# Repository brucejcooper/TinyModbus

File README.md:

# TinyModbus DALI Gateway

An ATtiny1604-based Modbus RTU to DALI gateway. It acts as a Modbus slave device and puts DALI frames on the wire on behalf of a master.

> ## The gateway is a stateless pipe
>
> **It caches nothing about the bus.** No arc levels, no status, no presence or
> dirty bitmaps, no group masks, no commissioning state, no scan cursors. The
> master submits opaque commands over a single function code; the gateway
> executes them in accept order and hands each result back exactly once, holding
> it until the master acks it. That is the whole contract.
>
> This is deliberate — "no cache of a cache": **the ballasts are the
> authority, the controller holds the one and only cache, the gateway holds
> none.** The consequences are worth stating plainly —
>
> - **A gateway reboot is consequence-free.** There is no state to lose, so the
>   class of bug where a rebooted gateway served zeroed registers and poisoned
>   the master's cache is structurally impossible, not merely mitigated.
> - **Board replacement loses nothing.** Swap the hardware, and the controller
>   re-establishes everything by querying the ballasts.
> - **Anything reading gateway state returns ILLEGAL DATA
>   ADDRESS** — see the register map below. A client still reading those
>   addresses is a version mismatch and should fail loudly rather than receive
>   plausible zeros.
>
> The one feature that may ever grow back gateway-side is an unsolicited-frame
> event ring for DALI-2 input devices, which needs the gateway to notice frames
> the master did not ask for.

The PCB design is in the `pcb` folder. It is set up to hold an RS-485 transceiver and the DALI bus driver circuitry on a compact board.

---

## DALI Protocol

### Overview

DALI (Digital Addressable Lighting Interface) is a two-wire serial lighting control protocol standardised as IEC 62386. It allows individual control of up to 64 ballasts/drivers on a single bus, with support for groups, scenes, and bidirectional communication (status queries).

### Physical Layer

DALI runs over a simple two-wire bus. Key characteristics:

| Parameter | Value |
|-----------|-------|
| Nominal bus voltage | 16 V DC |
| Operating range | 9.5 – 22.5 V |
| Max bus current | 250 mA |
| Max cable distance | 300 m |
| Max cable voltage drop | 2 V |
| Topology | Free-form (star, daisy-chain, mixed) — ring not allowed |
| Polarity | Insensitive (either wire can be "+" or "−") |

The bus is powered by a dedicated DALI power supply. Bus-powered devices (sensors, push-button interfaces) draw power directly from it.

Signal levels:
- Logic **1** (idle/high): 16 V ± 6.5 V
- Logic **0** (active/low): 0 V ± 4.5 V

### Manchester (Biphase) Encoding

DALI uses **Manchester encoding** (also called biphase encoding) at **1200 bps**.

Each bit period is 833 µs. The bit is split into two equal half-periods of **416.67 µs** each (called Te in the standard):

```
Logic 1:  LOW  for first half-bit, HIGH for second half-bit
          ___
     ___|   |

Logic 0:  HIGH for first half-bit, LOW for second half-bit
      ___
     |   |___
```

Manchester encoding guarantees a transition in the middle of every bit, which provides self-clocking and ensures the bus never stays continuously high or low for longer than one half-bit period. This also means the DALI power supply is delivering current for at least half the time during any transmission.

### Frame Format

**Forward frame** (controller → ballast): 1 start bit + 8 address bits + 8 data bits + 2 stop bits = **19 bits**, transmitted MSB first. Total duration ≈ 15.8 ms.

```
 S  A7 A6 A5 A4 A3 A2 A1 A0  D7 D6 D5 D4 D3 D2 D1 D0  P P
 |←─── address byte ────────→|←─── data byte ─────────→|
```

S = start bit (logic 1), P = stop bits (logic 1, return bus to idle)

**Backward frame** (ballast → controller): 1 start bit + 8 data bits + 1 stop bit = **10 bits**. Duration ≈ 9.95 ms. The ballast must respond within 7–22 Te (≈ 2.9 – 9.2 ms) after the forward frame ends.

### Address Byte Structure

```
 A7  A6  A5  A4  A3  A2  A1  A0
  |   |   |   |   |   |   |   |
  |   └───┴───┴───┴───┴───┘   └── Command type: 0=DAPC, 1=Command
  └─────────────────────────────── Address type: 0=Short, 1=Group/Broadcast
```

| A7 | A6–A1 | A0 | Meaning |
|----|-------|----|---------|
| 0  | addr (0–63) | 0 | Direct Arc Power Control (DAPC) to short address |
| 0  | addr (0–63) | 1 | Command to short address |
| 1  | group (0–15) | 0 | DAPC to group |
| 1  | group (0–15) | 1 | Command to group |
| 1  | 111111 | 0/1 | Broadcast (A0=0 → DAPC, A0=1 → command) |

A queued command carries the address byte verbatim, so short addresses, groups, broadcast and the special commands are all reachable through the queue — the gateway does not interpret any of them.

### Command Types

**Direct Arc Power Control (DAPC)** — sets light output immediately:
- Data byte: 0 = off, 1–254 = proportional level (logarithmic), 255 = no change

**Standard commands** (address byte LSB = 1) — the data byte selects the command:

| Command | Data byte | Description |
|---------|-----------|-------------|
| Off | 0x00 | Turn off (no fade) |
| Up | 0x01 | Fade up by one step at the configured fade rate |
| Down | 0x02 | Fade down by one step at the configured fade rate |
| Step Up | 0x03 | Step up one level (no fade) |
| Step Down | 0x04 | Step down one level (no fade) |
| Recall Max | 0x05 | Go to maximum level |
| Recall Min | 0x06 | Go to minimum level |
| Go To Last Active | 0x0A | Restore last non-zero level |
| Go To Scene N | 0x10–0x1F | Recall scene 0–15 |
| Reset | 0x20 | Reset to factory defaults |
| Set DTR0 | (special) | Loads a value into the data transfer register before a set command |
| Query Status | 0x90 | Returns 8-bit status byte (backward frame) |
| Query Actual Level | 0xA0 | Returns current arc power level (backward frame) |
| Query Max Level | 0xA1 | Returns max arc power level |
| Query Min Level | 0xA2 | Returns min arc power level |
| Query Power On Level | 0xA3 | Returns power-on default level |
| Query System Failure Level | 0xA4 | Returns system failure default level |
| Query Fade Time/Rate | 0xA5 | Returns fade settings |
| Query Groups 0–7 | 0xC0 | Returns bitmask of group membership |
| Query Groups 8–15 | 0xC1 | Returns bitmask of group membership |

**Set commands** (require value pre-loaded into DTR0, and must be sent twice within 100 ms to take effect):

| Command | Data byte | Description |
|---------|-----------|-------------|
| Set Max Level | 0x2A | Set maximum arc power level from DTR0 |
| Set Min Level | 0x2B | Set minimum arc power level from DTR0 |
| Set System Failure Level | 0x2C | Set level on bus/power failure |
| Set Power On Level | 0x2D | Set level on power restore |
| Set Fade Time | 0x2E | Set fade time from DTR0 |
| Set Fade Rate | 0x2F | Set fade rate from DTR0 |
| Add To Group N | 0x60–0x6F | Add device to group 0–15 |
| Remove From Group N | 0x70–0x7F | Remove device from group 0–15 |

### Status Byte (Query Status Response)

| Bit | Meaning |
|-----|---------|
| 0 | Ballast status (0=ok, 1=failure) |
| 1 | Lamp failure |
| 2 | Arc power on |
| 3 | Limit error (commanded level was below min or above max) |
| 4 | Fade running |
| 5 | Reset state |
| 6 | Missing short address |
| 7 | Power cycle event |

### Fade

DALI supports smooth transitions between light levels. Two parameters control fading:

- **Fade time**: fixed-duration transition (0–15, where 0 = instant, 1 = 0.7 s, doubling each step up to ~90 s)
- **Fade rate**: steps-per-second mode (0–15, where 0 = no fade, 1 = 358 steps/s down to 1 step/s)

### Groups and Scenes

**Groups (0–15):** A device can belong to multiple groups simultaneously (stored as a 16-bit bitmask). A single group command updates all members simultaneously in one DALI transmission — much faster than addressing devices individually.

**Scenes (0–15):** Each device stores 16 preset arc power levels. A "Go To Scene N" broadcast takes the entire installation to a preset state in one frame.

### Bus Timing Constraints

| Constraint | Value |
|------------|-------|
| Min inter-frame gap | ≥ 22 Te ≈ 9.2 ms |
| Backward frame response window | 7–22 Te after forward frame |
| Set command re-send window | ≤ 100 ms between the two required sends |
| DALI frame duration (forward) | ≈ 15.8 ms |
| DALI frame duration (backward) | ≈ 9.95 ms |

### Addressing and Commissioning

New or reset devices generate a 24-bit random address. A controller discovers and assigns short addresses (0–63) using a binary search algorithm:

1. Broadcast `RANDOMISE` to generate new random addresses
2. Repeat: set a search high address, issue `COMPARE` — devices with random address ≤ search address pull the bus low
3. Binary-search down to isolate one device
4. Issue `PROGRAM SHORT ADDRESS` to assign the next free address
5. Issue `YES` to confirm, then loop until no devices respond

Commissioning is **driven by the controller** over the command queue; this firmware only puts the frames on the wire. Out of scope for this firmware: 24-bit forward frames (DALI-2 control-device addressing), memory-bank reads, and DT1/DT8 device-type extensions.

---

## Architectural Model

The firmware is a **queue executor**. There is no work selector, no
reconciliation cache and no background polling: the only thing that ever causes
a DALI frame is a command the master enqueued.

```
Modbus master                     gateway                        DALI bus
  FC 0x41 enqueue  ──────────►  cmdq: command stamped seq n
                                       │
  reply: accept byte  ◄────────  ... + the head of the response queue
         + head entry                  │
                                 main loop: start_next_dali_work()
                                       │  head of cmdq, if respq has room
                                       ▼
                                 dali_sync: unpack [addr,data,flags,dtr0]
                                       │                            ──────►
                                       ▼                            ◄──────
                                 completion (ISR): cq_complete(seq,
                                       status, response8) → respq
                                       │
  FC 0x41 ack seq n  ─────────►  respq: entry n popped
```

**Command lifecycle** — `free → pending → executing`, and then the command is
gone. There is no terminal state, because a finished command is not a command:
it is an entry on the **response queue**, held under its sequence number until
the master acks it. The master never reads anything to discover a command
finished — the result arrives in the next reply.

**Execution order** is strict FIFO in accept order. The gateway stamps each
accepted command with a sequence number (1–31), which is the only identity a
command has.

**Backpressure.** The arbiter will not start a command unless the response queue
has a free entry, so a master that stops acking stalls DALI execution rather
than ever losing a result.

**Multi-frame atomicity.** `dali_busy` is held across a whole command, so a
`QF_DTR0` pair (`0xA3<dtr0>` then the frame) goes out back-to-back with nothing
interleaved. Commissioning — which is a long sequence of interdependent frames —
achieves the same exclusivity from the *controller* side by submitting one frame
at a time and admitting nothing else for that slave.

**Ordering guarantee (acceptance-critical).** `cq_complete` writes a response
entry's two bytes and only THEN publishes it by bumping a single-byte counter;
`cq_head` reads the counter before the entry. `cq_accept` writes the command
bytes and seq before publishing the slot as pending, and `cq_next` reads the
state before trusting them. A reader can therefore never see a published entry
holding stale bytes. There are no interrupt fences involved, deliberately —
every shared byte has exactly one writer, and a `cli` on this path is what
caused the 2026-06-05 RX-starvation incident.

**Bus-fault handling.** If the DALI line is held asserted past the escape
timeout (200 TE, ~83 ms), the in-flight command is completed `H_FAILED` with a
bus-fault code rather than abandoned — otherwise it would sit EXECUTING forever
and the master would wait on a command that can never finish.

### What moved to the controller, and why

| was in the gateway | now |
|---|---|
| `block0` arc/status cache | controller queries `QUERY STATUS` / `QUERY ACTUAL LEVEL` |
| present + dirty bitmaps | controller's presence model, with debounced evidence rules |
| group masks + ADD/REMOVE fan-out | controller diffs membership and emits the frames itself |
| per-ballast brightness bank | controller emits DAPC frames |
| boot scan, rescan cursor, scan trigger | controller's boot interrogation + background sweep |
| commissioning state machine | controller drives INITIALISE…TERMINATE as queued frames |

Size effect of the strip, measured at the time: **flash 15474 → 10014 bytes
(−35 %)**, **SRAM 532 → 171 bytes (−68 %)**. `g_regs` no longer exists — its
only fields were the four caches above. (For where the budget stands today, see
"Stack budget" under Known Limitations.)

---

## DALI State Machine

The firmware implements a five-state bit-level machine that drives all DALI bus activity. Every state transition is interrupt-driven — the main loop simply sleeps until a Modbus command arrives or a queued command is ready to dispatch.

### Timer Architecture

Two hardware timers underpin the state machine:

- **TCA0** — the half-bit clock. Runs continuously at 10 MHz with a period of exactly one DALI half-bit (416.67 µs). On each overflow it decrements a countdown (`dali_timer`) and fires a registered callback (`dali_timer_cb`) when the countdown reaches zero. This drives both transmission timing and state-machine timeouts. Runs at CPU interrupt level 0.
- **TCB0** — the pulse-width capture timer. Active only during the RECEIVING state. Configured in Frequency Measurement mode and fed by the DALI RX pin via the AVR event system. It captures the time between consecutive edges, giving the width of each Manchester pulse without CPU polling. Configured as CPU interrupt level 1 so it can preempt TCA0 mid-bit for accurate edge timestamping.

### States

```
                    ┌─────────────────────┐
       sync work    │        IDLE         │◄────────────────────────────┐
       pending      │  (dali_idle = true) │                             │
          ┌─────────┤  watch for external │                             │
          │         │  TX on RX pin       │                             │
          │         └──────────┬──────────┘                             │
          │                    │ rising edge on RX                      │
          ▼                    │ (another master transmitting)          │
  ┌───────────────┐            ▼                                        │
  │ TRANSMITTING  │    ┌───────────────┐      22 Te bus idle            │
  │               │    │ WAIT_FOR_IDLE ├──────────────────────────────►─┤
  │ TCA0 fires    │    │               │◄─────────────────────────────┐ │
  │ each half-bit │    │ watches for   │  after RECEIVING             │ │
  └───────┬───────┘    │ bus to settle │  (ok or malformed)           │ │
          │            └───────────────┘                              │ │
          │ all bits + stop bits sent                                 │ │
          ▼                                                           │ │
  ┌───────────────┐                                                   │ │
  │  WAIT_FOR_    │  no response within 22 Te ─────────────────────►──┘ │
  │  RESPONSE     │                              NAK → back to IDLE     │
  │               │  rising edge on RX                                  │
  └───────┬───────┘  (backward frame starting)                          │
          │                                                             │
          ▼                                                             │
  ┌───────────────┐  8 bits decoded + timeout                           │
  │  RECEIVING    ├───────────────────────────────────────────────────►─┘
  │               │  (RESPONSE_OK or MALFORMED → WAIT_FOR_IDLE)
  │  TCB0 pulse   │
  │  capture ISR  │
  └───────────────┘
```

### State Descriptions

**IDLE** (`dali_state_idle.c`)

The bus is quiet and we own it. The entry path branches on `dali_busy`:
- If `dali_busy` is true, a sync op is in flight and we just finished the inter-frame gap. Clear `dali_idle`, re-check the bus, and dispatch the next step of the in-flight op via `dali_sync_dispatch_current()` (which picks the right command for the current `OP_*` and calls `issue_dali_command`).
- Otherwise, `OUTCLR` the DALI TX line (belt-and-braces release), set `dali_idle = true` (allowing the main loop to sleep or to call `start_next_dali_work()` to launch a new sync op), prepare the receive timer, and arm a one-shot rising-edge interrupt on RX. If a rising edge arrives it means another master has started transmitting, so we yield via `dali_wait_for_idle_state_enter()` until the bus is quiet again.

**TRANSMITTING** (`dali_state_transmitting.c`)

Sends the 16-bit forward frame using Manchester encoding driven entirely by TCA0 callbacks:

1. Load the 16-bit command word into `shift_reg`, set `bits_left = 17`.
2. Schedule `send_one()` via `dali_timer = 1` (one half-bit tick).
3. `send_one()` drives TX high and schedules `half_bit_toggle()`.
4. `half_bit_toggle()` toggles TX (completing the mid-bit transition), schedules the next bit's first-half function (`send_one` or `send_zero` from the MSB of `shift_reg`), shifts `shift_reg` left, decrements `bits_left`.
5. When `bits_left == 0`, schedules `start_stop_bits()`, which drives TX low for 4 Te (two full stop bits).
6. After stop bits: CMD_QUERY and CMD_SEND_TWICE call `dali_wait_for_response_state_enter()`. CMD_SEND and CMD_DIRECT_ARC call `dali_result_received(DALI_RESPONSE_NAK, 0)` directly (no response expected; skips the 22 Te response window to halve inter-command latency).

Each bit takes exactly 2 TCA0 ticks (2 × 416.67 µs = 833.33 µs = 1200 bps).

**WAIT_FOR_RESPONSE** (`dali_state_wait_for_response.c`)

After the forward frame the master must listen for a backward frame within 7–22 Te. This state:
- Pre-configures TCB0 for pulse capture (`dali_state_receiving_prepare()`).
- Arms a one-shot rising-edge interrupt on RX. A rising edge means a backward frame start bit is arriving; we call `dali_state_receiving_enter()`.
- Sets a TCA0 timeout of 22 Te. If it fires before any edge, the device did not respond: call `dali_result_received(DALI_RESPONSE_NAK, 0)` and return to IDLE.

Commands that do not expect a response (e.g. DAPC, Off) still pass through this state; the NAK timeout simply confirms silence and the state machine moves on.

**RECEIVING** (`dali_state_receiving.c`)

Decodes the Manchester-encoded backward frame (8 data bits) using TCB0 pulse-width capture. Every edge on the RX pin triggers `TCB0_INT_vect`, which:
1. Reads the captured pulse width in timer ticks.
2. Classifies the pulse as *short* (≈ half-bit, ±20%) or *long* (≈ full-bit, ±20%). Pulses outside either window are errors.
3. Looks up the next state and the bit to shift into `shiftreg` from a compact transition table:

```
State       Short pulse → (next state, bit)   Long pulse → (next state, bit)
STARTBIT    MIDDLE_1,  no shift               ERROR
START_0     MIDDLE_0,  shift 0                ERROR
START_1     MIDDLE_1,  shift 1                ERROR
MIDDLE_0    START_0,   no shift               MIDDLE_1, shift 1
MIDDLE_1    START_1,   no shift               MIDDLE_0, shift 0
```

The *short* pulse is a half-bit transition (mid-bit); the *long* pulse spans a full bit and carries the same bit value as the previous bit (a "stretched" transition at the bit boundary).

TCA0 is re-armed to 5 Te on every edge. When TCA0 fires with no new edge — i.e. the bus has been idle for more than two full bits — `timer_overflow()` is called:
- If the final state is `START_0` or `MIDDLE_1` **and** exactly 8 bits were received: `dali_result_received(DALI_RESPONSE_OK, shift_reg)`.
- Otherwise: `dali_result_received(DALI_RESPONSE_MALFORMED, 0)`.

Either way, transitions to WAIT_FOR_IDLE to enforce the minimum inter-frame gap.

**WAIT_FOR_IDLE** (`dali_state_wait_for_idle.c`)

Enforces the DALI requirement that the bus be idle for at least 22 Te before the next forward frame. Works by watching the RX line:
- If the bus is high (shorted/active), arm a level-low interrupt and wait for release.
- Once the bus goes low (idle), start a TCA0 countdown of 22 Te.
- If the bus goes high again before the countdown expires (another master, collision debris, capacitive ringing), restart.
- When 22 Te completes uninterrupted: call `dali_idle_state_enter()`.

### Work selection

There is one source of DALI work: the command queue. Each main-loop pass, if the
bus is idle and no command is in flight, `start_next_dali_work()` takes the head
of the command queue — provided the response queue has room for its result —
marks it EXECUTING and dispatches it.

The sync-flag table, the rotating reconciliation cursor, the periodic rescan and
the priority chain that arbitrated between them are **not present**. The
gateway does no polling of its own, so the bus carries exactly the frames the
controller asked for and nothing else — which is also why bus utilisation is now
a property the controller can reason about and tune.

### Multi-Master Behaviour

The firmware detects transmissions from other DALI masters on the bus: if a rising edge arrives on RX while in IDLE, the state machine yields by entering WAIT_FOR_IDLE. It waits for the other master's transaction (forward frame + optional backward frame) to complete and the bus to settle for 22 Te before re-asserting control. The firmware does not implement active collision detection during its own transmissions.

---

## Modbus Interface

### Connection

Modbus RTU, RS-485, 8N1.

Slave address and baud rate live in USERROW so they survive a chip erase + reflash. The factory-fresh (post-erase) USERROW value of `0xFF` maps to address 1 / 9600 baud; `make configure` writes 38400 unless told otherwise. Writes to holding registers 0x1F02 / 0x1F03 trigger a USERROW page-erase-write; the runtime baud/slave switch is deferred until the FC06/FC10 response we are about to send has cleared the wire, so the master sees the response at the old config and the next request at the new one.

### Function codes

| Code | Name | Use |
|---|---|---|
| 0x03 | Read Holding Registers | USERROW config registers (max 16 regs per request) |
| 0x04 | Read Input Registers | version / RX diagnostics / sysinfo / queue counters |
| 0x06 | Write Single Holding Register | a config or action register (0x1F00+) |
| 0x10 | Write Multiple Holding Registers | a contiguous holding block — config registers only |
| 0x41 | **Queue** (user-defined) | **the command queue** — enqueue a DALI command and/or ack a result, in one transaction |

Everything else gets an `ILLEGAL FUNCTION` (0x01) reply. That includes coils
(FC01 / FC05 / FC0F), which were never supported, and **FC23 (0x17), which was
the queue path under v2 and is now gone entirely** — a controller still speaking
FC23 is a version mismatch and is meant to fail loudly. FC 0x41 is user-defined
per MODBUS V1.1b (codes 65–72 and 100–110 are reserved for user definition), so
it is a conformant code rather than an extension: framing, CRC, silence and
exception replies are all ordinary RTU, and only the payload shape is custom.

### Register map

The map is deliberately small, and **the command queue is not in it**. Under v4
commands and acks travel as FC 0x41 payload, not as register writes, so there is
nothing here to poll. **Nothing exposes gateway state**; addresses outside this
table return ILLEGAL DATA ADDRESS (0x02) — a client reading them is a version
mismatch and should fail loudly rather than get plausible zeros.

Every FC04 block is an **exact-length** read: the counts below are the only ones
accepted, and any other count is ILLEGAL DATA ADDRESS rather than a short read.
`src/registers.h` is authoritative.

| Address | FC | Width | Content |
|---|---|---|---|
| `0x0200–0x020F` | 04 | 16 regs | Version string `DALI v<maj>.<min> <20-hex-serial>`. Read exactly 16. |
| `0x0210–0x021F` | 04 | 16 regs | Build string: the `git describe --long --dirty --tags` the image was built from (e.g. `v0.5-81-gabc1234`), ASCII, NUL-padded to 32 bytes. `-dirty` = built from an uncommitted tree. Read exactly 16. |
| `0x0300–0x030F` | 04 | 16 regs | RX diagnostics: `reg0` rx_overflow, `reg1` frame_error, `reg2` crc_error (a CRC-good frame addressed to another device is ignored, framing errors included; any CRC-bad frame counts, since its address can't be trusted), `reg3` frames_ok, `reg4` last_fail_len, `reg5–12` the last CRC-failed frame, `reg13` internal fault count, `reg14` `[tm_err_t \| tm_fault_site_t]` of the first internal fault. Zeroed on reset. Read exactly 16. |
| `0x0310–0x0313` | 04 | 4 regs | Sysinfo: `reg0–1` uptime_s (32-bit BE), `reg2` boot_count (since cold power-on), `reg3` reset_reason (`RSTCTRL.RSTFR`: bit0 PORF, 1 BORF, 2 EXTRF, 3 WDRF, 4 SWRF, 5 UPDIRF). No EEPROM — uptime is RAM, boot_count is magic-guarded `.noinit`, reset_reason is hardware-latched. Read exactly 4. |
| `0x0320–0x0327` | 04 | 8 regs | **Queue counters** (new in v4). Read exactly 8 — see "Queue diagnostics" below. |
| `0x1F02` | 03, 06 | 1 reg | Modbus slave address (1–247). USERROW-persisted, applied on reboot. |
| `0x1F03` | 03, 06 | 1 reg | Baud index: 0 = 9600, 1 = 19200, 2 = 38400. USERROW-persisted, applied after the ACK. |
| `0x1F05` | 06 | 1 reg | System reset. Write `0xA5A5` to force a software reset once the ACK has left the wire. Any other value → ILLEGAL DATA **VALUE** (0x03) — the register exists, the value was wrong (`registers.c` returns `TM_ERR_BAD_VALUE`). |

**Retired — all return ILLEGAL DATA ADDRESS:**

| Address | Was |
|---|---|
| `0x0000–0x003F` | per-ballast status\|brightness (the arc-level bank). The controller emits DAPC frames through the queue instead. |
| `0x0040–0x00FF` | per-ballast config banks. |
| `0x0100–0x0103` | present bitmask |
| `0x0104–0x0107` | dirty bitmask |
| `0x0110–0x014F` | group membership masks |
| `0x1000–0x100F` | **v2 command block** (8 slots × 2 registers). Retired with queue v4: commands are FC 0x41 payload now. |
| `0x1010–0x1017` | **v2 slot status block** (one register per slot). Retired with queue v4: results come back in the FC 0x41 reply. |
| `0x1F00` | SCAN_TRIGGER |
| `0x1F01` | RESCAN_INTERVAL |
| `0x1F04` | COMMISSION trigger/status |

### The command queue (FC 0x41)

**`QUEUE-PROTOCOL.md` is the normative specification** — what follows describes
what the device offers, not the contract's fine print. `src/fc41.h` is the wire
format in code.

One function code carries all queue traffic. A request optionally **enqueues**
one DALI command and optionally **acks** (deletes) the head of the gateway's
**response queue**. The reply reports the fate of the enqueue — an **accept
byte** carrying a gateway-assigned sequence number — and the current **head** of
the response queue. In steady state that is one ~14-byte transaction per DALI
frame: each request enqueues one command, acks the previous result and collects
the next.

#### Frame formats

Every packed byte has the same shape — **control in the top 3 bits, sequence in
the low 5**. Sequences run **1–31**; `0` is reserved and means "none" (no ack
requested, no seq assigned, queue empty).

```
 bit   7    5   4          0
     ┌───────┬───────────────┐
     │ ctl:3 │     seq:5     │
     └───────┴───────────────┘
```

**Request — 5, 7 or 8 bytes** (CRC included):

```
┌─────┬──────┬─────────────────┬──────┬──────┬──────┬────────┬────────┐
│slave│ 0x41 │ [flags:3|ack:5] │ addr │ data │ dtr0 │ CRC lo │ CRC hi │
└─────┴──────┴─────────────────┴──────┴──────┴──────┴────────┴────────┘
                                └── enqueue payload, 7–8 B frames ──┘
```

Flags occupy bits 7–5 of the third byte: `QW_TWICE` 0x80, `QW_DTR0` 0x40,
`QW_ANSWER` 0x20. (These are the **wire** positions and are deliberately not the
internal `QF_*` bits the DALI adapter tests; the parser normalises between them.)
`ack` is the low 5 bits: if non-zero, delete the head of the response queue iff
the head's seq matches. A mismatch is a silent no-op — the head reported in the
reply is all the master needs to re-converge — which is what makes an
ack-carrying frame safe to resend verbatim after a timeout.

| length | meaning | validity rule |
|---|---|---|
| **5 B** | ack and/or poll, no enqueue | flags must be `000` |
| **7 B** | enqueue without DTR0 preload (+ optional ack) | `QW_DTR0` clear |
| **8 B** | enqueue with DTR0 preload (+ optional ack) | `QW_DTR0` set |

Any other length, or a length/flag inconsistency, is **discarded without a
reply** and counted in `q_discard`, exactly as a corrupt frame would be — to the
master the two are indistinguishable and share one recovery path. The length
rule is not tidiness: the DTR0 flag is what decides whether byte 5 is a payload
byte or the first CRC byte, so a crafted length must not be able to walk
through. The check is the pure function `fc41_len_ok()` in `src/fc41.h`, which
the host test enumerates exhaustively. Broadcast (address 0) is silently
ignored — an enqueue is inherently addressed, because the reply carries the
binding.

**Reply — 6 or 7 bytes.** The accept byte is present **iff the request attempted
an enqueue**; the shape follows the *request*, not the outcome, so an `A_FULL`
reply is still 7 bytes. The master always knows which to expect because it sent
the request.

```
7 B:  slave, 0x41, [astatus:3|aseq:5], [hstatus:3|hseq:5], resp8, CRC lo, CRC hi
6 B:  slave, 0x41,                     [hstatus:3|hseq:5], resp8, CRC lo, CRC hi
```

- **Accept byte** — the fate of *this* enqueue. `A_ACCEPTED` (0) means enqueued
  and `aseq` (1–31) is the command's identity; `A_FULL` (1) means the command
  queue was full, nothing was enqueued and `aseq` is 0.
- **Head entry** — the oldest unacked result, unchanged until acked. `hseq` = 0
  means the response queue is empty. With `hstatus` = `H_OK` (0), `resp8` is the
  backward-frame answer (or 0 for a command that expected none); with `hstatus`
  = `H_FAILED` (1), `resp8` is a failure code: `0x01` NAK (no or too-short
  backward frame where one was expected), `0x02` COLLISION (garbled backward
  frame — two or more gear answered), `0x03` BUSFAULT (stuck/shorted bus only — any reply that fails to decode, pulse-width errors included, is COLLISION).
  COLLISION is distinct from NAK so the controller's any-on probe can read a
  collision as "≥1 on" and silence as "none on".

**There are no Modbus exceptions on this path.** A full command queue is
reported in band as `A_FULL` rather than as an exception, because an exception
would throw away the head report in the same breath — and the head is exactly
what tells the master a slot has freed. It also leaves nothing for a transport
auto-retry to latch onto.

#### Processing order

Per accepted request, **strictly**: **ack → enqueue → build the reply**. That
order is part of the protocol, not an implementation detail. Acking first frees
a response-queue entry that the same transaction's enqueue can then use, which
is what makes one transaction per DALI frame achievable; any other order costs a
whole Modbus transaction per frame.

#### Two queues

| | depth | holds |
|---|---|---|
| command queue | `CMDQ_DEPTH` = **2** | 1 executing + 1 pending. Accepted commands, executed strict FIFO in accept order. |
| response queue | `RESPQ_DEPTH` = **4** | results, **retained until acked**. Steady-state occupancy is 2. |

A command's whole life is `free → pending → executing`; when it finishes it is
no longer a command but a response-queue entry, and its slot is free. Both
depths are build-time constants and **nothing on the wire depends on them** —
the master's in-flight cap is matched on its own side. (Raising `CMDQ_DEPTH` is
not the one-line change it looks like; see the depth note in
`QUEUE-PROTOCOL.md` §0.)

**Backpressure.** The arbiter will not start a command unless the response queue
has a free entry: a full response queue **stalls DALI execution rather than ever
dropping a result**. The master always has a way out, because the ack is
processed before the enqueue — one transaction frees an entry and refills the
pipeline.

**Sequence numbers are assigned exclusively by the gateway.** The master never
proposes one; it learns each command's identity from the accept byte. A seq
stays pinned in the gateway until its result is acked, and acks are head-only
and in order, so a live seq cannot recur without a reboot.

#### Reboots

The gateway keeps **nothing** across a reboot — no queues, no sequence counter,
no ledger — and that is the point: the counter simply restarts and the master
learns the new numbers. There is nothing to reconcile.

The master detects a reboot from **sequence behaviour**: an accept byte
returning a seq it still tracks, or a head bearing a seq it never submitted, are
each proof of a restart, backed by the **`boot_count`** register (FC04 `0x0310`)
as the cold-path arbiter for the one genuinely ambiguous case. The v2 rule —
"a slot the master believed active reads back idle, so the gateway rebooted" —
is gone with the slots. `QUEUE-PROTOCOL.md` §4 has the full rule set and the
order they must be evaluated in.

#### The DALI adapter (the payload contract)

The queue itself is **DALI-agnostic**: it carries an opaque 4-byte command and
returns an 8-bit response. What those bytes mean is the DALI adapter's contract,
and it is what the request's enqueue payload becomes:

```
addr    DALI forward-frame address byte (any: short / group / broadcast / special)
data    DALI forward-frame data byte
flags   QW_TWICE   — send the forward frame twice, no answer (SET / INITIALISE / RANDOMISE)
        QW_DTR0    — emit 0xA3<dtr0> back-to-back immediately before the frame
        QW_ANSWER  — open the backward-frame window; resp8 = the 8-bit answer
dtr0    value preloaded into DTR0 when QW_DTR0 is set; absent otherwise
```

The parser rewrites the wire flags into the internal `QF_*` bits the adapter
tests (`queue_flags_to_qf` in `modbus.c`) — the two sets have deliberately
different bit positions, and only the `QW_*` values above appear on the wire.

The address byte can be anything valid — short address, group, broadcast (0xFE),
or a special such as 0xA3 SET_DTR0 or the commissioning specials. The gateway
does not interpret it and has no cache to invalidate: what a command *means* is
entirely the controller's business. A `QW_DTR0` command's two frames land
back-to-back with nothing interleaved; other DALI work waits behind the pair
(~2 frame times).

#### Queue diagnostics (FC04 `0x0320`, read exactly 8)

Nothing rides the FC 0x41 reply beyond the protocol's own bytes — hot-path bytes
are the scarce resource — so the queue's observability lives here, in cold-path
registers meant to be read on demand from the CLI or the bench, never polled
hot. All eight are 16-bit **wrapping** counters, big-endian:

| reg | name | counts |
|---|---|---|
| `0x0320` | `accepts` | commands enqueued (`A_ACCEPTED` replies) |
| `0x0321` | `a_full` | enqueues refused, command queue full (`A_FULL` replies) |
| `0x0322` | `executes` | commands handed to the DALI adapter |
| `0x0323` | `results` | results pushed onto the response queue |
| `0x0324` | `acks` | response entries popped by a matching ack |
| `0x0325` | `stalls` | backpressure episodes — arbiter refusals caused by a full response queue |
| `0x0326` | `q_discard` | FC 0x41 frames dropped with no reply (bad length or length/flag inconsistency) |
| `0x0327` | spare | reads 0 |

Steady-state sanity is `accepts == executes == results == acks`, each lagging
the one before it by at most the queue depths. Three of them want reading
carefully, and two of them point in **opposite** directions:

- **`a_full` non-zero is an anomaly worth investigating, not routine
  back-pressure.** It means the master's pacing estimate ran early — it offered
  a command while the gateway was still full. The queue handled it correctly
  (that is what the in-band `A_FULL` is for) but a correctly paced master should
  not be producing them.
- **`stalls` non-zero is just backpressure working.** It counts *episodes* (the
  rising edge, not every arbiter poll) and simply says the master stopped
  acking for long enough to fill the response queue. Not alarming by itself;
  it is also the counter the backpressure test reads to prove the rule engaged.
- **`q_discard` non-zero means malformed FC 0x41 frames arrived** — a bad length
  or a length/flag inconsistency. It lives here rather than in the RX
  diagnostic block because it is a protocol fact, not a line fact. A discard is
  invisible from the master's side by design, so this counter is the only place
  it shows up.

#### Why v4 exists

Measured on the bench against the FC23 design v4 replaces, at saturation:

| | FC23 | v4 |
|---|---|---|
| RS-485 bus occupancy | **99 %** | **37 %** |
| Modbus transactions per DALI command | 1.73 | 1.03 |
| throughput (DTR0 write/read pairs per second) | 14.71 | ~13.9–14.1 |

Throughput is essentially unchanged — it was always bounded by DALI, not by
Modbus — but it now costs about a third of the bus instead of all of it. That
headroom is the whole point: it is what makes a second DALI gateway on the same
RS-485 segment workable.

### Commissioning

`MBREG_COMMISSION` (0x1F04) and the gateway's binary-search state machine are
**removed**. The controller drives the whole IEC 62386-102 sequence —
INITIALISE, RANDOMISE, SEARCHADDRH/M/L, COMPARE, PROGRAM SHORT ADDRESS, VERIFY,
WITHDRAW, TERMINATE — as ordinary queued frames. No tight inter-step timing is
involved: the gear's INITIALISE window is 15 minutes against a run of tens of
seconds.

Two behaviours the gateway implementation discovered on hardware are preserved
in the controller port, and are easy to get wrong if it is ever reimplemented:

- **COMPARE is anyone-pulls-low.** ANY decoded response means "at least one gear
  matched"; only a clean no-answer means "none". A collided/garbled backward
  frame is a match, not an error.
- **After a bit-0 COMPARE says "no"**, the gear's SEARCHADDR registers hold the
  bit-0-cleared value while the master's copy has bit 0 restored. The search
  address must be **re-sent** before PROGRAM, or PROGRAM addresses nothing and
  VERIFY fails.

See `controller/src/dali_commission.c`.

### Write propagation and fade tracking

The gateway reports one thing per command: the result that lands on the response
queue under that command's sequence number. It does not track fades, does not
re-poll, and has no dirty bit to raise — those were properties of the cache it
no longer has.

**Fade tracking is the controller's job.** A DAPC lands immediately but the
level ramps, so the controller re-reads `QUERY STATUS` while bit 4 (FADE
RUNNING) is set and only then trusts the level. See `dali_state.c`.

### Multi-Master Operation

The firmware is designed to operate as the sole DALI master on its bus. It can detect when another master is transmitting (rising edge on the RX pin) and will yield rather than collide — but it does not decode traffic it did not initiate, and it keeps no register state that could go stale.

If another DALI master changes ballast levels, the **controller's** cache is what drifts, and it re-converges on its background sweep (one ballast per `dali_sweep_interval_ms`, default 10 s) or on the next command's post-command verification. Tune that interval controller-side if an installation genuinely has a second master.

---

## Hardware

### Pin Assignment (ATtiny1604)

| Pin | Signal |
|-----|--------|
| PA1 | RS-485 TX (USART0 alternate TXD) |
| PA2 | RS-485 RX (USART0 alternate RXD) |
| PA4 | RS-485 DE — driver enable, driven by hardware RS-485 mode (USART_RS485_EXT_gc), no firmware management needed |
| PB0 | DALI TX — drives the external bus transistor. **OUTSET (PB0 HIGH) asserts the bus** (drives bus low via the transistor); **OUTCLR (PB0 LOW) / high-Z releases**. Reset state (high-Z) is released. |
| PB1 | DALI RX — input via optocoupler (signal is inverted: HIGH = bus active/low) |

### Power

The current board runs at 3.3 V, 10 MHz. It spends the majority of its time in Standby sleep mode, consuming under 1 µA. The watchdog timer resets the device if it hangs for more than 8.2 seconds.

**Board revision in progress (12 V → 5 V buck).** The present supply — an **HT7533 LDO** dropping 12 V to 3.3 V — **thermally shuts down under sustained DALI activity** (e.g. an inventory scan): 8.7 V × ~0.1 A in a SOT-89 overheats, the rail collapses, and the ATtiny browns out (this is what the new FC04 `0x0310` reset-reason counter exposed — repeated `BORF` reboots during a scan). The fix is a **synchronous buck (MP2331H, LCSC C6992878)** to a **5 V** rail, which also enables 20 MHz operation and stronger RS-485 drive. Full root-cause analysis, the power-supply BOM, the supply-current budget, and the firmware changes the 5 V/20 MHz board needs (F_CPU, clock prescaler, **BOD → 4.2 V**, DALI bit-timing re-verify) are documented in `CLAUDE.md` → "Power supply — board revision".

---

## Building

The project uses a bundled AVR-GCC toolchain in `avr/bin/` — do not use the system or Homebrew avr-gcc, as they lack ATtiny1604 support and produce incorrect results. Download the bundled toolchain once with:

```sh
make download_gcc
```

Then build and flash:

```sh
make build   # compile only
make         # build, erase device, and flash
```

`pymcuprog` is required for flashing. Programming is via UPDI on the test point using a USB-UART adapter.

A standard `make` (build + erase + flash) does NOT touch USERROW — the slave address and baud rate persist across reflashes. To write the persisted-config bytes:

```sh
make configure                                              # defaults: address 1, 38400 baud
make configure SLAVE_ADDR=5 BAUD_INDEX=1                    # address 5, 19200 baud (legacy)
make configure SLAVE_ADDR=42 BAUD_INDEX=2
```

`BAUD_INDEX` is `0=9600 / 1=19200 / 2=38400`. `make configure` rewrites all 32 USERROW bytes — the four config bytes plus 28 bytes of `0xFF`.

## Known Limitations

These are residual issues that the current firmware does not address. None are runtime-fatal; each has a documented workaround or expected impact.

### Modbus

- **Inter-byte timeout conflated with inter-frame.**  Modbus §2.5.1.1 wants a 1.5-char inter-byte gap to declare a frame malformed and a separate 3.5-char inter-frame silence to mark frame end.  This firmware uses a single threshold sized for 3.5-char silence ({10, 6, 6} TCA0 ticks at 9600/19200/38400), so bytes arriving 2–3 char apart are silently accepted as part of one frame and rely on the CRC check to reject.  Any master that streams its bytes contiguously is unaffected.
- **FC10 partial execution on register-map holes.**  The holding-register map is now just 0x1F02, 0x1F03 and 0x1F05, so everything between and around them is a hole — including 0x1F04, which sits between two live registers.  A multi-register write spanning a hole aborts on the first invalid address with `ILLEGAL_ADDRESS`, leaving earlier registers in the same FC10 already written and dispatched.  Workaround: write the config registers one at a time with FC06, which is what the controller does.
- **FC04 0x0200 returns an ASCII version string, not a register address space.**  Reading exactly 16 input registers from address 0x0200 yields the 32-byte string `"DALI v<maj>.<min> <serial>"`.  Other lengths at this address fall through to the standard register-range check and return `ILLEGAL_ADDRESS`.
- **`frame_is_valid` recognises the unsupported coil function codes (FC01 / FC05 / FC0F) for size-check purposes, and the broadcast filter still admits FC05 / FC0F.**  This is intentional: well-formed coil frames pass frame validation, reach the FC dispatcher, and receive a graceful `ILLEGAL_FUNCTION` exception reply (or — for a broadcast-addressed FC05 / FC0F — are silently absorbed) rather than being dropped at the size check.  Candidate for future tightening: removing the FC01 / FC05 / FC0F cases from `frame_is_valid` and from the broadcast filter would drop those frames at validation time instead.  Nothing breaks if it stays as-is; the current shape gives masters that probe for coil support a clearer "function not supported" answer.

### DALI

- **No multi-master collision detection during our own TX.**  If another master begins driving the bus while we are already transmitting, the resulting collision is not detected; the receiving ballast simply sees a malformed frame and ignores it.
- **Receiver dead-band.**  Half-bit and full-bit pulse classification has a ±83 µs tolerance window (`DALI_HALF_BIT_USECS / 5`); pulses falling between the half-bit and full-bit ranges (~500–750 µs) are reported as `PULSE_IN_MIDDLE`.  A single gear at spec-compliant bit timing never produces one; several gear answering at once (a group query, COMPARE, two gear sharing an address) produce them routinely, so any receive error is reported to the master as COLLISION — something answered.
- **A queued DTR0-first command holds the bus for its pair.**  A command with the `QW_DTR0` flag issues two frames (`0xA3<dtr0>` then the frame, e.g. a config DTR0+SET pair) as one atomic unit, so DTR0 can't be clobbered between them.  Other DALI work waits behind the pair (~2 frame times).  Single-frame commands (DAPC level, group-bit changes, most raw commands) are unaffected — ≤ ~50 ms each.  (The old 6-send `SYNC_WRITE_MINMAX/POWER/FADE` sequences were retired with the config banks.)

### Hardware / runtime

- **Stack budget — not a constraint on this firmware.**  Static allocation is **153 B** of the 1024 B SRAM (`.data + .bss + .noinit`, per `avr-size`), leaving **871 B** for the stack; flash is **10 472 / 16 384 B**.  The gateway caches nothing about the bus, which is what keeps it small: the whole queue core (command queue 12 B, response queue 8 B, counters 12 B, cursors 5 B) is 37 B, and the 40 B Modbus `buf` is the single largest item.  The deepest measured frame is `modbus_process` at 48 B (`-fstack-usage`, `dynamic,bounded` — the `snprintf` in the FC04 version-string path), and the worst nested-ISR chain (TCA0 LVL0 + TCB0 LVL1 on top of it) adds ~35 B, so real worst-case use is ~110 B against 871 B available.  These `.su` figures are per-frame, not cumulative — for a hard peak-stack number run a call-graph stack analyzer.  If a new ISR vector is added, check the `.su` files first.  `CLAUDE.md` → "RAM budget" carries the same breakdown and the two must move together.
- **RS-485 DE pin floats briefly at reset.**  `main` drives PA4 low immediately, but there is a ~50–200 µs window after reset (before that store executes) where the pin is high-Z.  Subtask 1 enabled the BOD fuse at 2.6 V, narrowing the window by holding the chip in reset until Vcc is stable; an external pull-down on PA4 on the next PCB revision is the residual recommended fix.
- **`USERROW` write halts the CPU.**  A `MBREG_SLAVE_ADDR` / `BAUD_INDEX` write performs a NVMCTRL page-erase-write that suspends CPU execution for ~3.4 ms.  Triggered by Modbus writes the firmware schedules so the halt lands in the master's silence window before our response, but a DALI frame in flight at that exact moment will be corrupted.  Avoid changing config during heavy DALI traffic.

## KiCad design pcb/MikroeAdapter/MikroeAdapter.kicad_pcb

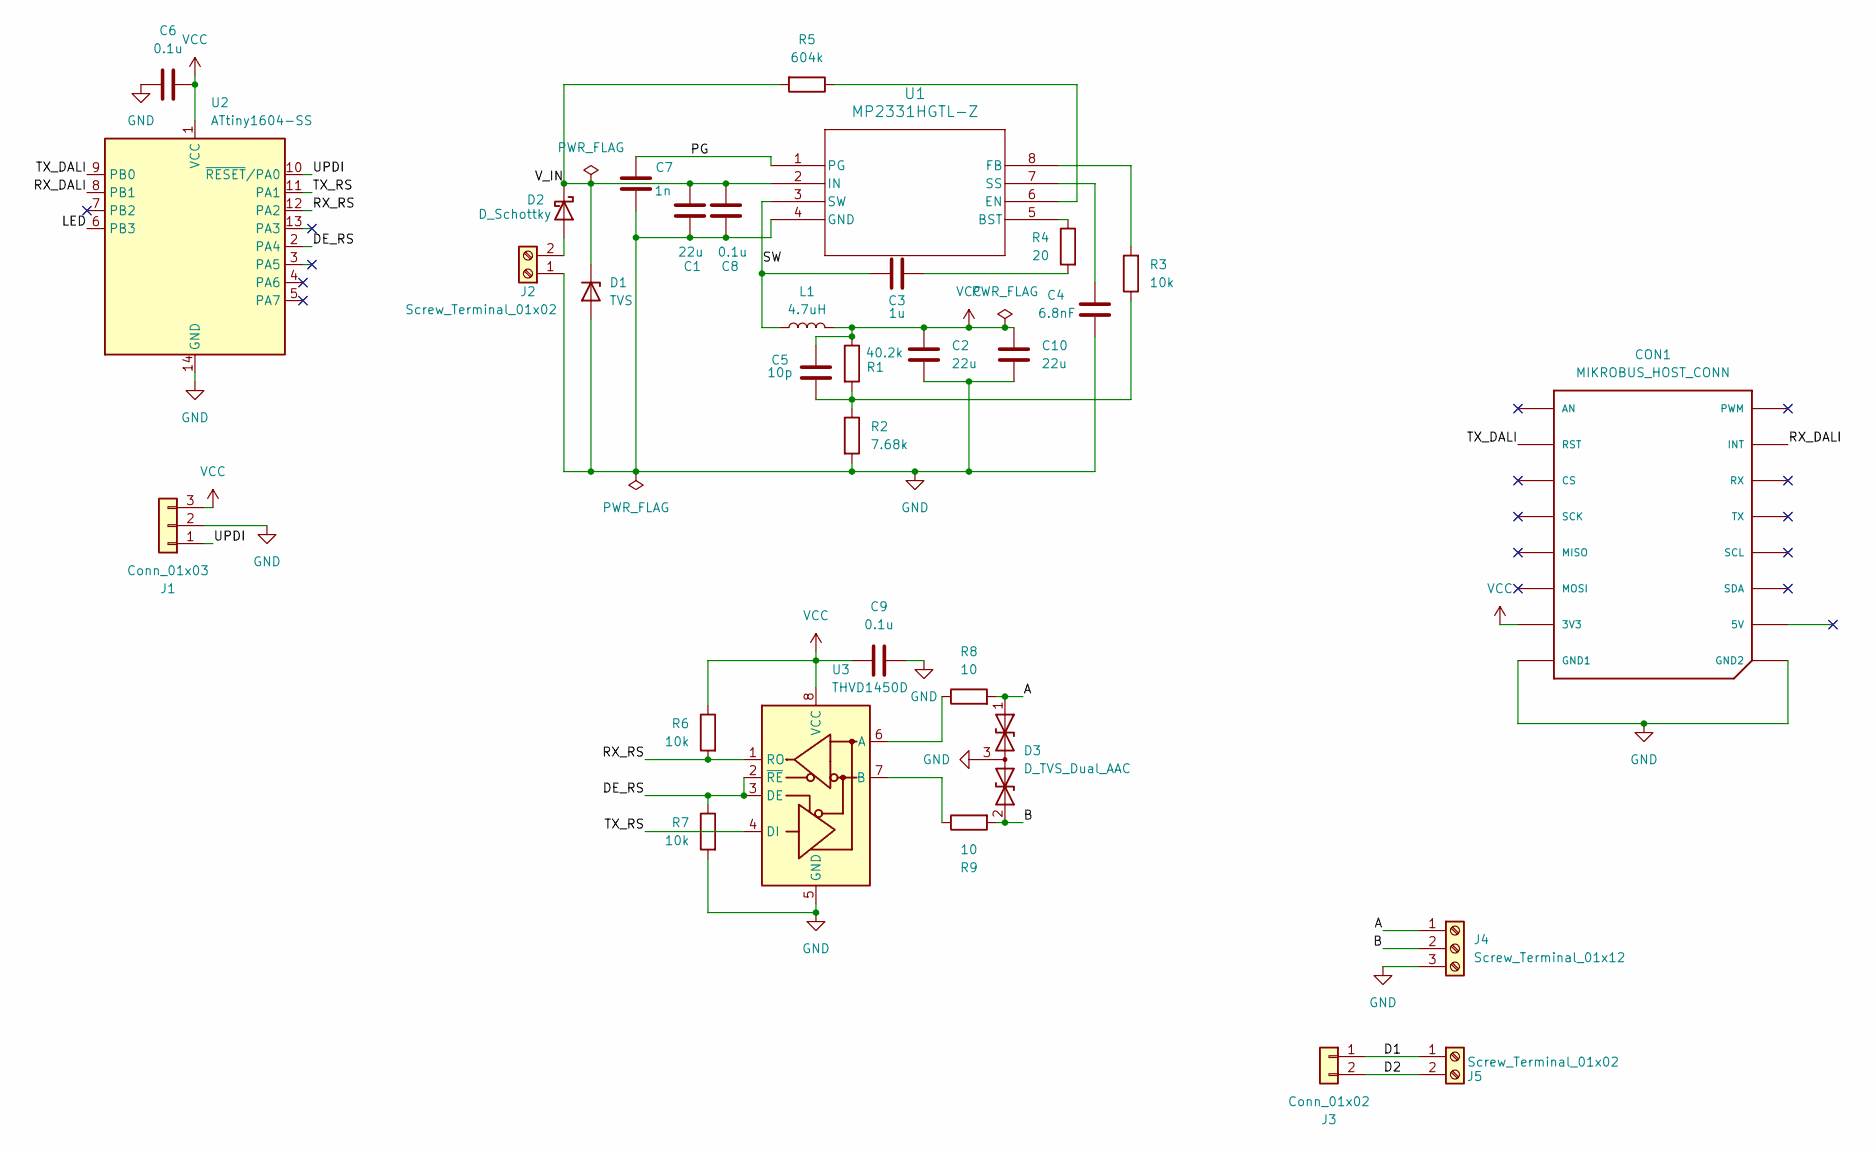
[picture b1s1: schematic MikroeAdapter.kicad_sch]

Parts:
C1, C2, C10: 22u; C_1210_3225Metric
C3: 1u; C_0603_1608Metric
C4: 6.8nF; C_0603_1608Metric
C5: 10p; C_0402_1005Metric
C6, C8, C9: 0.1u; C_0402_1005Metric
C7: 1n; C_0402_1005Metric
CON1: MIKROBUS_HOST_CONN
D1: TVS; D_SMB
D2: D_Schottky; D_SMA
D3: D_TVS_Dual_AAC; SOT-23
J1: Conn_01x03; PinHeader_1x03_P2.54mm_Vertical
J2, J5: Screw_Terminal_01x02; TerminalBlock_Phoenix_MKDS-1,5-2-5.08_1x02_P5.08mm_Horizont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
J3: Conn_01x02; PinHeader_1x02_P2.54mm_Vertical
J4: Screw_Terminal_01x12; TerminalBlock_Phoenix_MKDS-1,5-3-5.08_1x03_P5.08mm_Horizont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
L1: 4.7uH; IND-SMD_L4.0-W4.0_FNR40XXS
R1: 40.2k; R_0402_1005Metric
R2: 7.68k; R_0402_1005Metric
R3: 10k; R_0402_1005Metric
R4: 20; R_0402_1005Metric
R5: 604k; R_0402_1005Metric
R6, R7: 10k; R_0805_2012Metric
R8, R9: 10; R_0603_1608Metric
U1: MP2331HGTL-Z; SOT-583-8
U2: ATtiny1604-SS; SOIC-14_3.9x8.7mm_P1.27mm
U3: THVD1450D; SOIC-8_3.9x4.9mm_P1.27mm

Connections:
/A: D3.1 (A1), J4.1, R8.2
/B: D3.2 (A2), J4.2, R9.2
/D1: J3.1, J5.1
/D2: J3.2, J5.2
/DE_RS: R7.1, U2.2 (PA4), U3.2 (~RE), U3.3 (DE)
/LED: U2.6 (PB3)
/PG: C7.1, U1.1 (PG)
/RX_DALI: CON1.P15 (INT), U2.8 (PB1)
/RX_RS: R6.2, U2.12 (PA2), U3.1 (RO)
/SW: C3.2, L1.1, U1.3 (SW)
/TX_DALI: CON1.P2 (RST), U2.9 (PB0)
/TX_RS: U2.11 (PA1), U3.4 (DI)
/UPDI: J1.1, U2.10 (~RESET/PA0)
/V_IN: C1.1, C8.1, D1.1 (K), D2.1 (K), R5.2, U1.2 (IN)
GND: C1.2, C2.2, C4.1, C6.1, C7.2, C8.2, C9.1, C10.2, CON1.P8 (GND1), CON1.P9 (GND2), D1.2 (A), D3.3 (common), J1.2, J2.1, J4.3, R2.2, R7.2, U1.4 (GND), U2.14 (GND), U3.5 (GND)
unnamed: C3.1, R4.2
unnamed: C5.2, R1.2, R2.1, R3.1
unnamed: D2.2 (A), J2.2
unnamed: R4.1, U1.5 (BST)
unnamed: R5.1, U1.6 (EN)
unnamed: R3.2, U1.8 (FB)
unnamed: C4.2, U1.7 (SS)
unnamed: R8.1, U3.6 (A)
unnamed: R9.1, U3.7 (B)
VCC: C2.1, C5.1, C6.2, C9.2, C10.1, CON1.P7 (3V3), J1.3, L1.2, R1.1, R6.1, U2.1 (VCC), U3.8 (VCC)

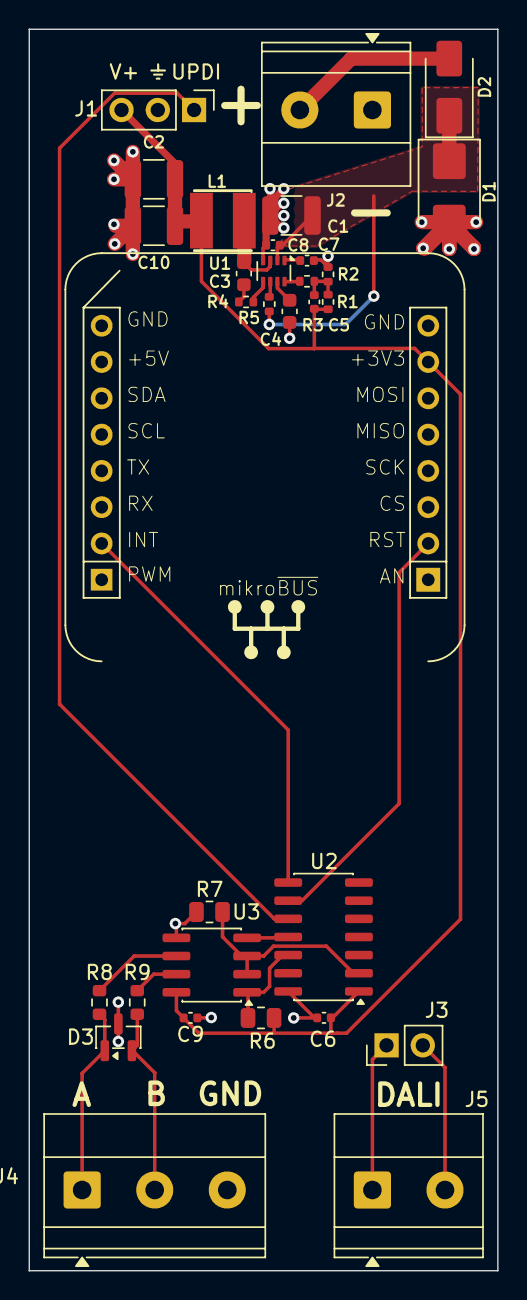
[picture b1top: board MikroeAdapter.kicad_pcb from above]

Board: 2 copper layers, 32.8 x 86.9 mm, 32 parts (0 on the bottom side), 24 nets.

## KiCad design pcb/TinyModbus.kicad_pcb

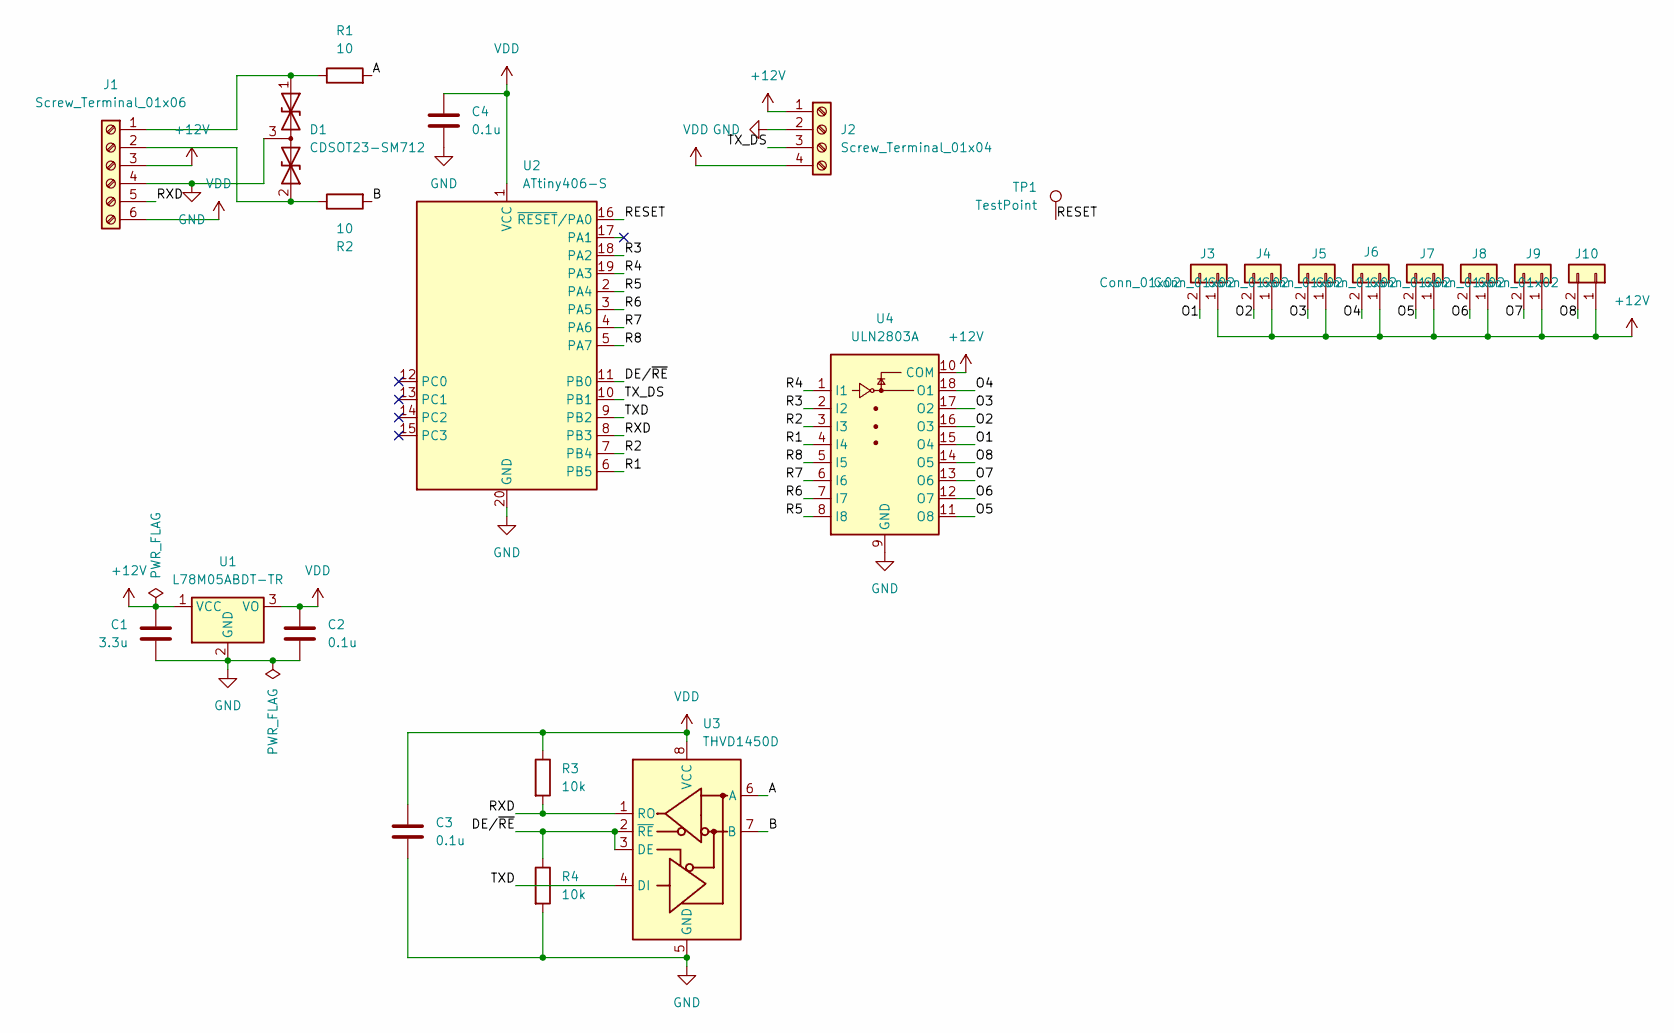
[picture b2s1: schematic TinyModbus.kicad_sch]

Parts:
C1: 3.3u; C_0805_2012Metric
C2, C3, C4: 0.1u; C_0805_2012Metric
D1: CDSOT23-SM712; SOT-23-3
J1: Screw_Terminal_01x06; TerminalBlock_Phoenix_MKDS-1,5-6-5.08_1x06_P5.08mm_Horizont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
J2: Screw_Terminal_01x04; TerminalBlock_Phoenix_MKDS-1,5-4-5.08_1x04_P5.08mm_Horizont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
J3, J4, J5, J6, J7, J8, J9, J10: Conn_01x02; Terminal_lug
R1, R2: 10; R_0805_2012Metric
R3, R4: 10k; R_0805_2012Metric
TP1: TestPoint; TestPoint_THTPad_2.0x2.0mm_Drill1.0mm
U1: L78M05ABDT-TR; TO-252-2
U2: ATtiny406-S; SOIC-20W_7.5x12.8mm_P1.27mm
U3: THVD1450D; SOIC-8_3.9x4.9mm_P1.27mm
U4: ULN2803A; SOP-18_7x12.5mm_P1.27mm

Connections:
+12V: C1.1, J1.3, J2.1, J3.1, J4.1, J5.1, J6.1, J7.1, J8.1, J9.1, J10.1, U1.1 (VCC), U4.10 (COM)
/A: R1.2, U3.6 (A)
/B: R2.2, U3.7 (B)
/DE/~RE: R4.1, U2.11 (PB0), U3.2 (~RE), U3.3 (DE)
/O1: J3.2, U4.15 (O4)
/O2: J4.2, U4.16 (O3)
/O3: J5.2, U4.17 (O2)
/O4: J6.2, U4.18 (O1)
/O5: J7.2, U4.11 (O8)
/O6: J8.2, U4.12 (O7)
/O7: J9.2, U4.13 (O6)
/O8: J10.2, U4.14 (O5)
/R1: U2.6 (PB5), U4.4 (I4)
/R2: U2.7 (PB4), U4.3 (I3)
/R3: U2.18 (PA2), U4.2 (I2)
/R4: U2.19 (PA3), U4.1 (I1)
/R5: U2.2 (PA4), U4.8 (I8)
/R6: U2.3 (PA5), U4.7 (I7)
/R7: U2.4 (PA6), U4.6 (I6)
/R8: U2.5 (PA7), U4.5 (I5)
/RESET: TP1.1, U2.16 (~RESET/PA0)
/RXD: J1.5, R3.2, U2.8 (PB3), U3.1 (RO)
/TXD: U2.9 (PB2), U3.4 (DI)
/TX_DS: J2.3, U2.10 (PB1)
GND: C1.2, C2.2, C3.2, C4.2, D1.3 (common), J1.4, J2.2, R4.2, U1.2 (GND), U2.20 (GND), U3.5 (GND), U4.9 (GND)
unnamed: D1.1 (A1), J1.1, R1.1
unnamed: D1.2 (A2), J1.2, R2.1
VDD: C2.1, C3.1, C4.1, J1.6, J2.4, R3.1, U1.3 (VO), U2.1 (VCC), U3.8 (VCC)

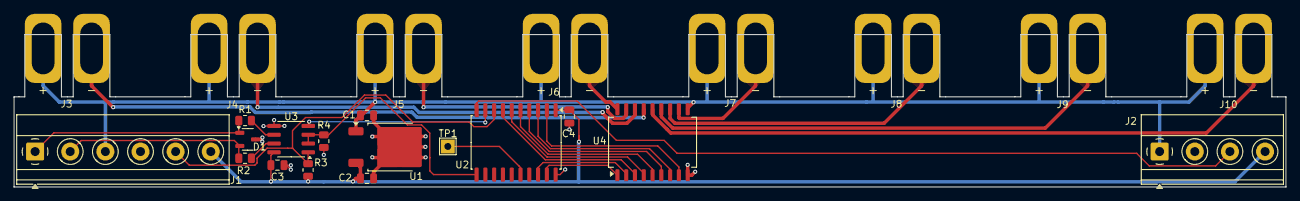
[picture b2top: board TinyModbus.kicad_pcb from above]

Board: 2 copper layers, 183.9 x 22.0 mm, 24 parts (0 on the bottom side), 28 nets.

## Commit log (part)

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2025-05-25 Committing something so that the makefile works
2025-05-31 Working sleeping 8 bit controller
2025-05-31 Added get_coils, for the 8 bits that this thing handles only
2025-05-31 Add README.md
2025-05-31 added pdb
2025-05-31 More info
2025-05-31 Adding links
2025-05-31 More doco
2025-05-31 Added picutre of PCB
2025-05-31 more readme
2025-10-10 Switching the name of the base to DTF08a
2025-10-10 Checkpoint before changing it to an adapter
2025-10-13 Got DALI and RS485 all working well enough. It does a basic scan
2025-10-13 Added some
2025-10-15 Many bug fixes, but it now accepts DALI commands directly, as used by the web configuration device
2025-10-15 Moved web app into repository
2025-10-19 Sleeps between commands
2025-10-19 Reworked web-ui
2025-10-19 missed a few files
2025-10-20 Switch to Production (hahardware, and using tick based timer, instead of trying software bollocks
2025-11-03 Fixed ISR bug, and changed web client to use entity editors, rather than just device editors that made assumptions about the entities contained
2025-11-05 all Async all the time
2025-11-26 Latest web changes
2025-11-30 Moved to vite
2025-12-02 Bug fixes around register mapping. Also added a WDT
2025-12-29 staging for moving to another server
2025-12-29 Added websocket server to the wrong host
2026-04-19 syncing with version on git
2026-04-19 Attempt to fix issues plaguing existing install
2026-04-27 Addititonal bugs claude keeps on finding, plus I removed mention of brightness of 0xFF indicating non-presence
2026-04-29 Removed ambiguous - characters
2026-04-29 Removing ambiguous x characters
2026-05-02 Bumped version number
2026-05-03 Getting ready for tasks
2026-05-03 Subtask 6: final README pass + verification + move task to done/
    Wraps up the flag-driven refactor (task #1). Documentation-only edits
    plus housekeeping; no source-code changes in this commit.
    README changes
    --------------
    - New top-level "## Architectural Model" section placed immediately
    before "## DALI State Machine". Four paragraphs explaining the
2026-05-16 Reduced size of row to fit in 32 bytes
2026-06-03 Debugged baud rate issues at 38400. It is now working reliably at 19200
2026-06-07 dali_sync: poll level until valid AND settled (fixes 255 after GOTO_LAST_ACTIVE)
    Wire-proven on the DALI bus (Saleae, Manchester-decoded; forward frames validated
    against the known opcodes): after GOTO_LAST_ACTIVE a ballast answers QUERY ACTUAL
    LEVEL with 0xFF (DALI MASK / "level not available") for the brief window before the
    fade starts — status still 0x00 (not fading) — then flips to FADING (0x14) and real
    ramping levels. The old OP_LEVEL_READ read that single 0xFF, saw not-fading, stopped,
    and stored 255, which propagated all the way to HA as 100%.
2026-06-17 Switched to buck converter for power so that we can run effectively off 12V
